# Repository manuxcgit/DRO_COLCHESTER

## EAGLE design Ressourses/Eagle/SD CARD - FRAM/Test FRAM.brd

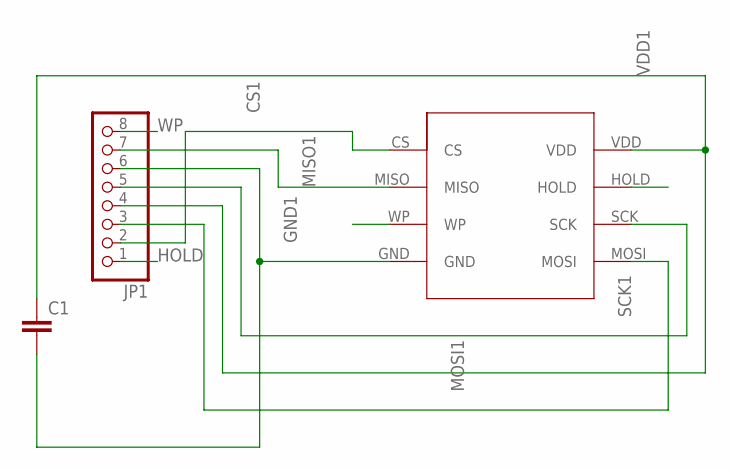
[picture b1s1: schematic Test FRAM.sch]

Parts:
C1: C-EU025-040X050; C025-040X050
JP1: PINHD-1X8; 1X08
U$1: MB85RS; SOIC8

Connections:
CS1: JP1.2, U$1.CS
GND1: C1.2, JP1.6, U$1.GND
HOLD: JP1.1, U$1.HOLD
MISO1: JP1.7, U$1.MISO
MOSI1: JP1.3, U$1.MOSI
SCK1: JP1.5, U$1.SCK
VDD1: C1.1, JP1.4, U$1.VDD
WP: JP1.8, U$1.WP

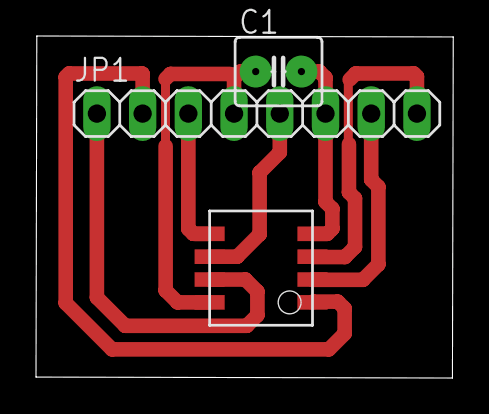
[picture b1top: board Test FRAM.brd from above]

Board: 2 copper layers, 23.2 x 19.0 mm, 3 parts (0 on the bottom side), 8 nets.

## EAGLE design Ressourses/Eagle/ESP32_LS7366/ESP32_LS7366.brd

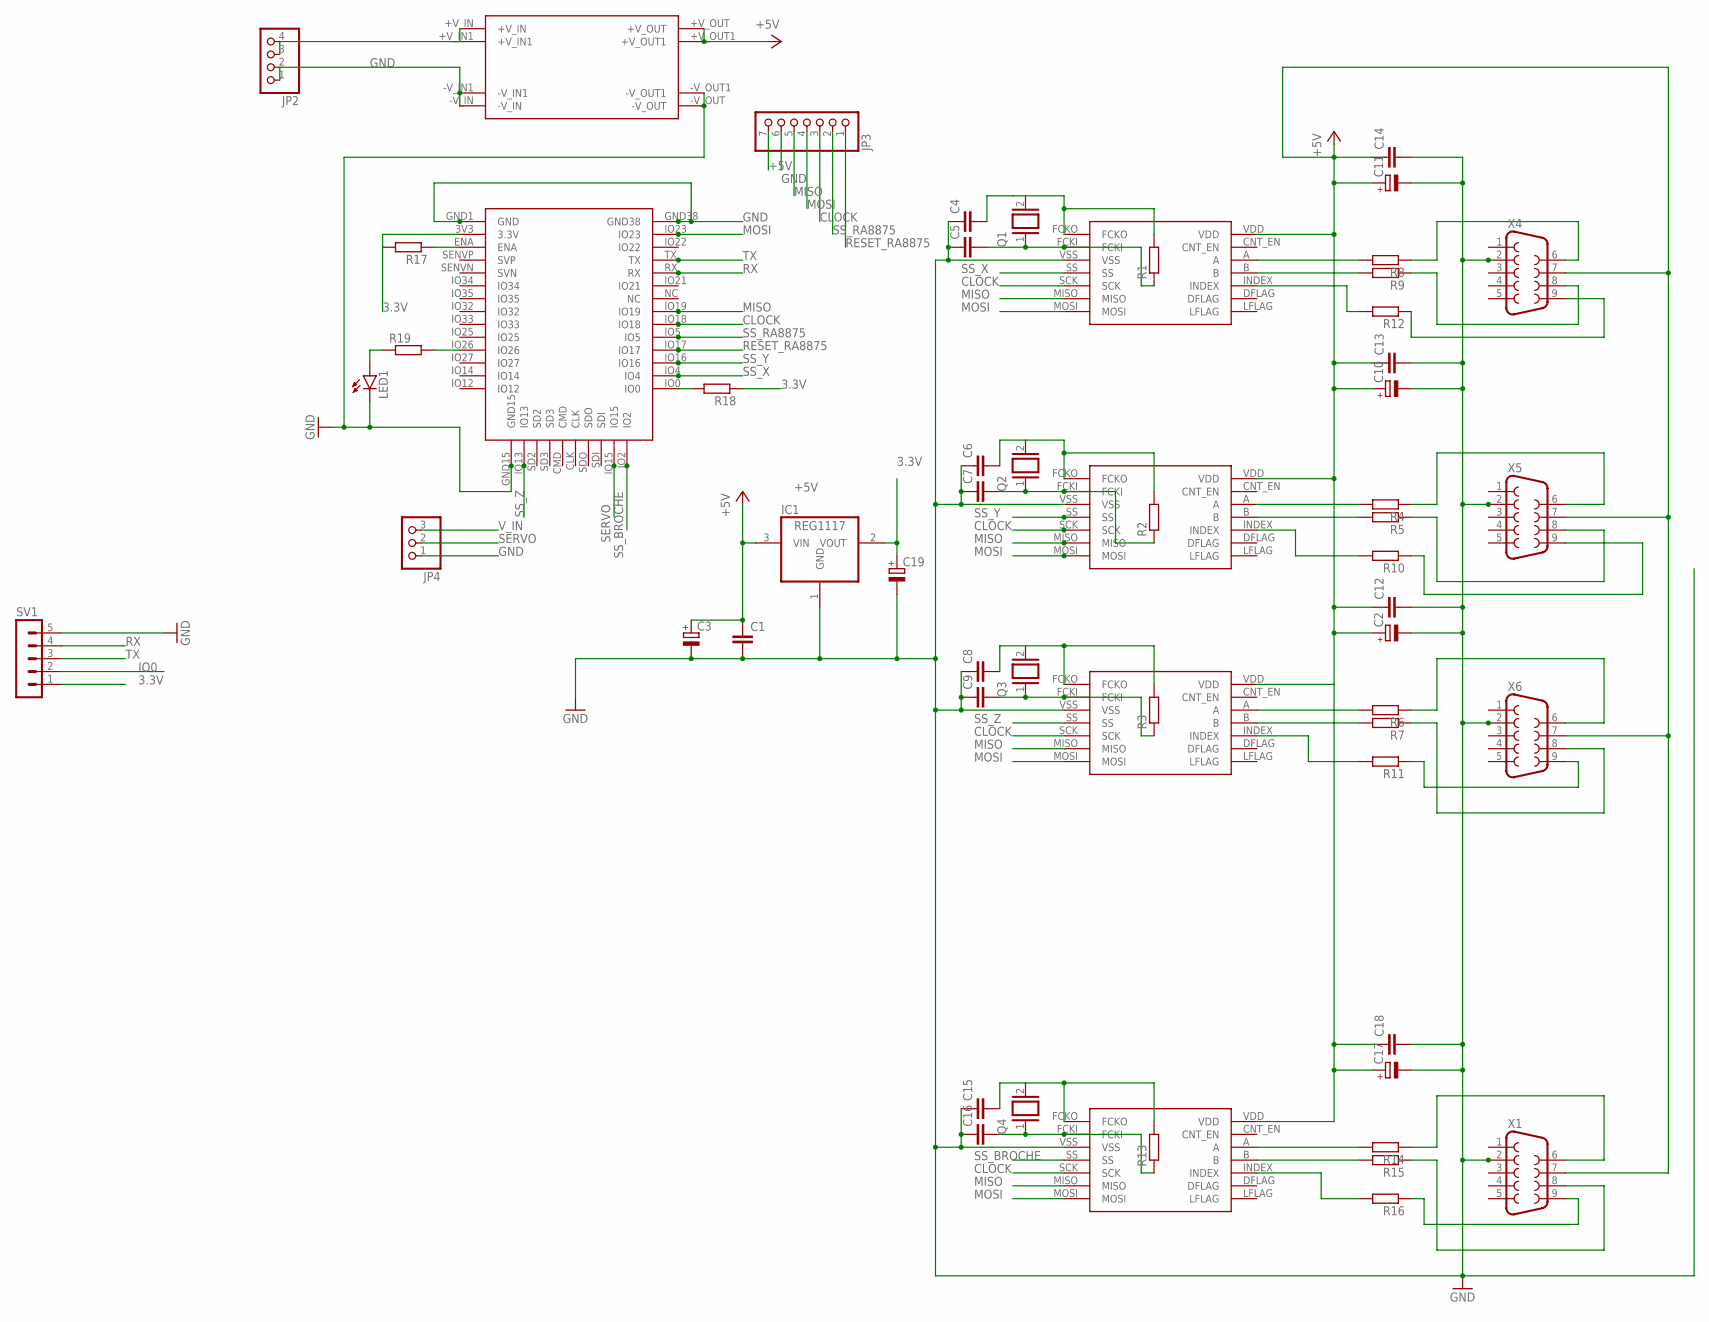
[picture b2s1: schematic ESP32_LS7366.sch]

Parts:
C1, C12, C13, C14, C18: C-EU050-035X075; C050-035X075
C2, C3, C10, C11, C17, C19: CPOL-EUE5-5; E5-5
C4, C5, C6, C7, C8, C9, C15, C16: C2.5/5; C2.5-5
IC1: REG1117; SOT223
JP2: PINHD-1X4; 1X04
JP3: PINHD-1X7; 1X07
JP4: PINHD-1X3; 1X03
LED1: LED3MM
Q1, Q2, Q3, Q4: XTAL/S; QS
R1, R2, R3, R4, R5, R6, R7, R8, R9, R10, R11, R12, R13, R14, R15, R16, R17, R18, R19: R-EU_0207_10; 0207/10
SV1: MA05-1
U$1, U$2, U$3, U$4: LS7366; DIP14
U$5: MODULE5V
U$6: ESP32MODULE; ESP32-MODULE
X1, X4, X5, X6: F09HP

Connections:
3.3V: C19.+, IC1.2 (VOUT), R17.2, R18.1, SV1.1, U$6.3V3 (3.3V)
+5V: C1.1, C2.+, C3.+, C10.+, C11.+, C12.1, C13.1, C14.1, C17.+, C18.1, IC1.3 (VIN), JP3.7, U$1.VDD, U$2.VDD, U$3.VDD, U$4.VDD, U$5.+V_OUT, U$5.+V_OUT1, X1.7, X4.7, X5.7, X6.7
CLOCK: JP3.3, U$1.SCK, U$2.SCK, U$3.SCK, U$4.SCK, U$6.IO18
GND: C1.2, C2.-, C3.-, C4.1, C5.1, C6.1, C7.1, C8.1, C9.1, C10.-, C11.-, C12.2, C13.2, C14.2, C15.1, C16.1, C17.-, C18.2, C19.-, IC1.1 (GND), JP2.1, JP2.2, JP3.6, JP4.1, LED1.K (C), SV1.5, U$1.VSS, U$2.VSS, U$3.VSS, U$4.VSS, U$5.-V_IN, U$5.-V_IN1, U$5.-V_OUT, U$5.-V_OUT1, U$6.GND1 (GND), U$6.GND15, U$6.GND38, X1.2, X4.2, X5.2, X6.2
IO0: R18.2, SV1.2, U$6.IO0
MISO: JP3.5, U$1.MISO, U$2.MISO, U$3.MISO, U$4.MISO, U$6.IO19
MOSI: JP3.4, U$1.MOSI, U$2.MOSI, U$3.MOSI, U$4.MOSI, U$6.IO23
unnamed: R4.1, X5.6
unnamed: R19.2, U$6.IO26
unnamed: C7.2, Q2.1, R2.1, U$3.FCKI
unnamed: LED1.A, R19.1
unnamed: C9.2, Q3.1, R3.1, U$4.FCKI
unnamed: R6.1, X6.6
unnamed: R7.1, X6.8
unnamed: R5.1, X5.8
unnamed: C5.2, Q1.1, R1.1, U$2.FCKI
unnamed: R8.1, X4.6
unnamed: R9.1, X4.8
unnamed: R8.2, U$2.A
unnamed: R7.2, U$4.B
unnamed: R4.2, U$3.A
unnamed: R5.2, U$3.B
unnamed: C4.2, Q1.2, R1.2, U$2.FCKO
unnamed: C6.2, Q2.2, R2.2, U$3.FCKO
unnamed: C8.2, Q3.2, R3.2, U$4.FCKO
unnamed: R12.2, U$2.INDEX
unnamed: R12.1, X4.9
unnamed: R10.2, U$3.INDEX
unnamed: R10.1, X5.9
unnamed: R11.2, U$4.INDEX
unnamed: R11.1, X6.9
unnamed: R6.2, U$4.A
unnamed: R9.2, U$2.B
unnamed: C16.2, Q4.1, R13.1, U$1.FCKI
unnamed: R14.1, X1.6
unnamed: R15.1, X1.8
unnamed: R15.2, U$1.B
unnamed: C15.2, Q4.2, R13.2, U$1.FCKO
unnamed: R16.2, U$1.INDEX
unnamed: R16.1, X1.9
unnamed: R14.2, U$1.A
unnamed: R17.1, U$6.ENA
RESET_RA8875: JP3.1, U$6.IO17
RX: SV1.4, U$6.RX
SERVO: JP4.2, U$6.IO15
SS_BROCHE: U$1.SS, U$6.IO2
SS_RA8875: JP3.2, U$6.IO5
SS_X: U$2.SS, U$6.IO4
SS_Y: U$3.SS, U$6.IO16
SS_Z: U$4.SS, U$6.IO13
TX: SV1.3, U$6.TX
V_IN: JP2.3, JP2.4, JP4.3, U$5.+V_IN, U$5.+V_IN1

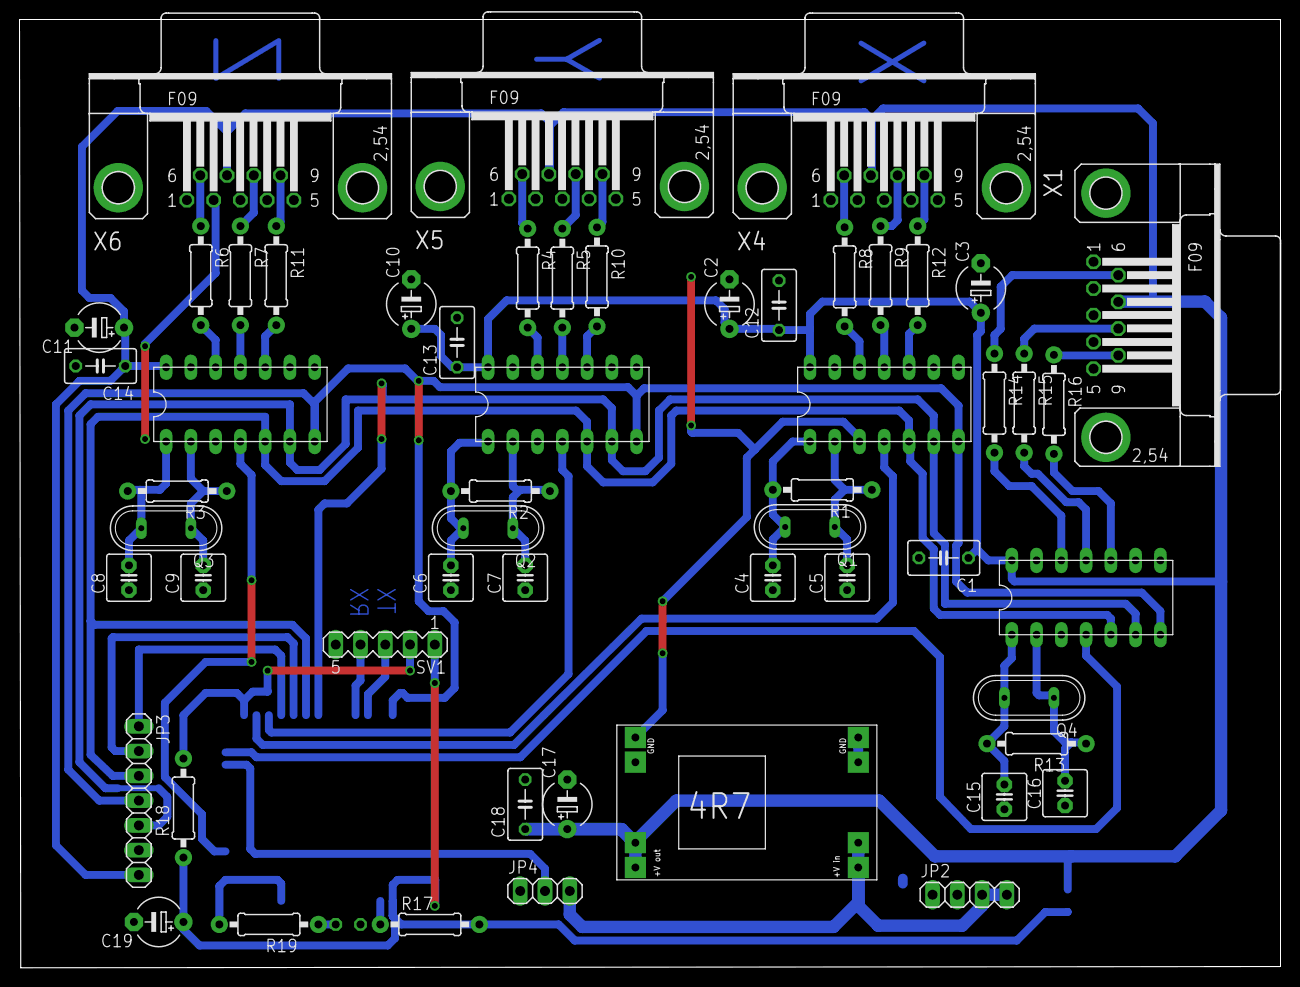
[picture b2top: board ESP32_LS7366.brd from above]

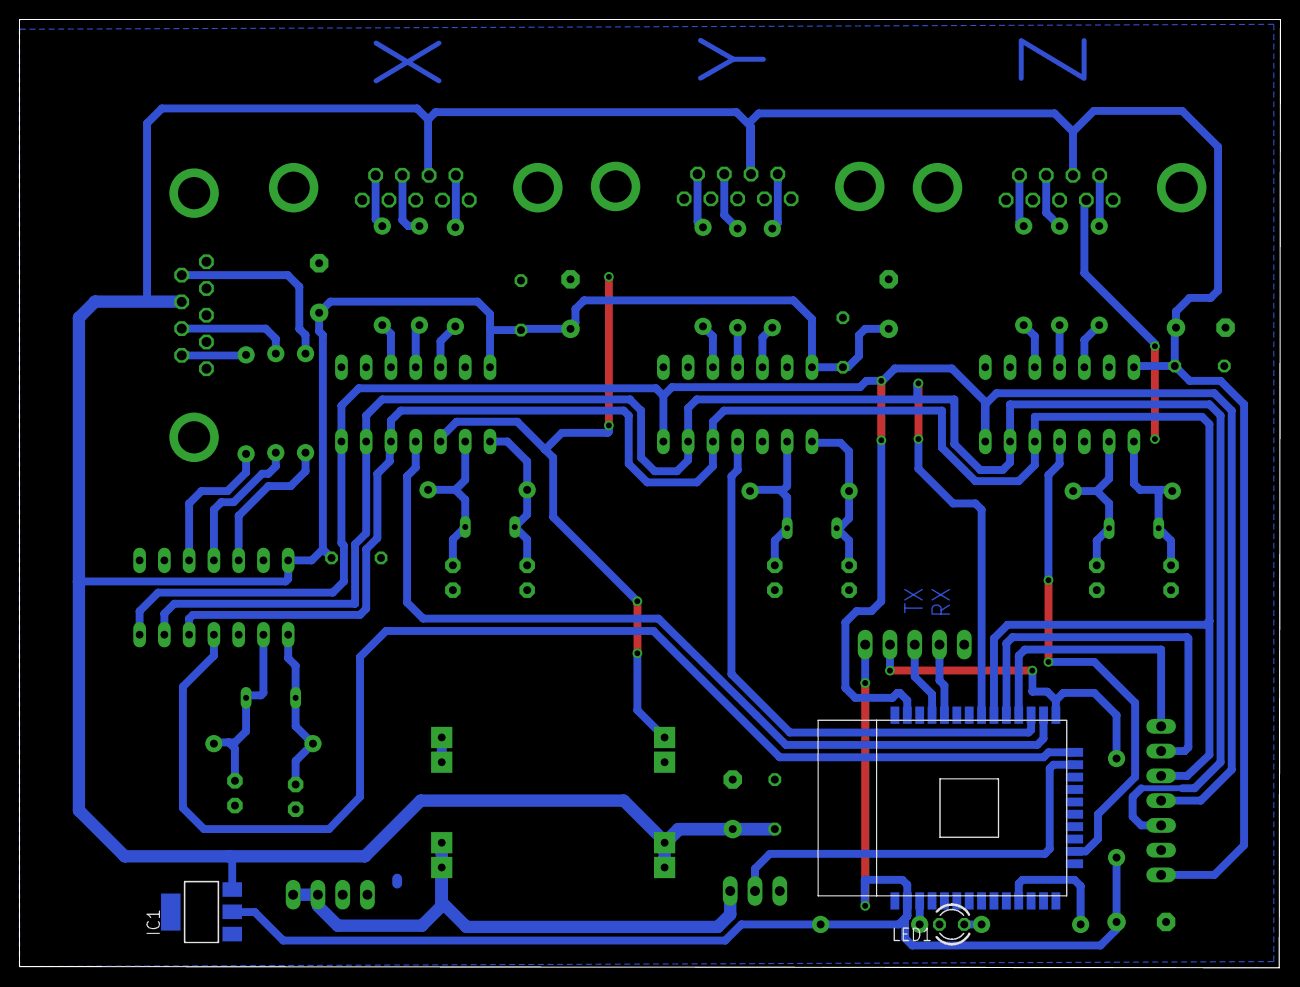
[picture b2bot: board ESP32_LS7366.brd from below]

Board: 2 copper layers, 129.3 x 97.3 mm, 58 parts (3 on the bottom side), 52 nets.

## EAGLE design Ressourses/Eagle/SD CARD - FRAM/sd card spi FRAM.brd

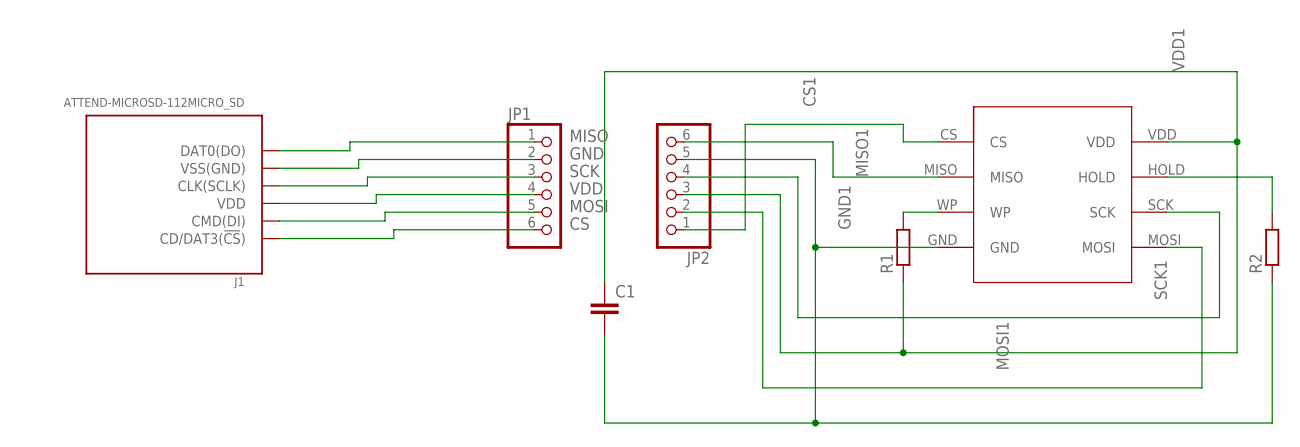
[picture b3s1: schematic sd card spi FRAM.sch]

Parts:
C1: C5/5; C5B5
J1: ATTEND-MICROSD-112MICRO_SD; MICROSD_MICROSD_CARD
JP1, JP2: PINHD-1X6; 1X06
R1, R2: R-EU_0207_10; 0207/10
U$1: MB85RS; SOIC8

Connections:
CS: J1.2 (CD/DAT3(!CS!)), JP1.6
CS1: JP2.1, U$1.CS
GND: J1.6 (VSS(GND)), JP1.2
GND1: C1.2, JP2.5, R2.1, U$1.GND
MISO: J1.7 (DAT0(DO)), JP1.1
MISO1: JP2.6, U$1.MISO
MOSI: J1.3 (CMD(DI)), JP1.5
MOSI1: JP2.2, U$1.MOSI
unnamed: R1.2, U$1.WP
unnamed: R2.2, U$1.HOLD
SCK: J1.5 (CLK(SCLK)), JP1.3
SCK1: JP2.4, U$1.SCK
VDD: J1.4 (VDD), JP1.4
VDD1: C1.1, JP2.3, R1.1, U$1.VDD

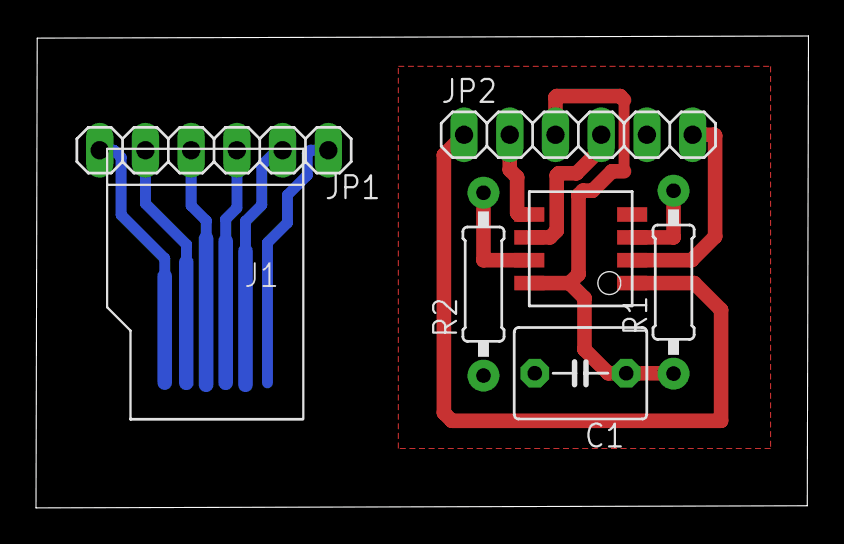
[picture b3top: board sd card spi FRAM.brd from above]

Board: 2 copper layers, 42.9 x 26.2 mm, 7 parts (0 on the bottom side), 14 nets.

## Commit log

2024-09-05 from Pharma
2024-09-16 many
2024-09-19 Usinage.com
